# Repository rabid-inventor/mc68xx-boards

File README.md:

# mc68xx-boards
collection of PCB's based around the Motorola MC6800 series processor

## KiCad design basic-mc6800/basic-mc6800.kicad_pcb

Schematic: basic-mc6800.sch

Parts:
C1, C2, C3, C5, C6, C7, C8, C9: C_Small; C_0603
J1: Conn_01x39_Male; PinHeader_1x39_P2.54mm_Vertical
J2: Conn_01x04_Male; PinSocket_1x04_P2.54mm_Vertical
JP1, JP2, JP3: Jumper_2_Open; SolderJumper-2_P1.3mm_Bridged_RoundedPad1.0x1.5mm
MH1, MH2, MH3, MH4: MountingHole; MountingHole_3.2mm_M3_DIN965
R1, R2, R3, R4, R5, R6, R7, R8: R_Small; R_0603_1608Metric
U1: 74LV32; SOIC-14_3.9x8.7mm_Pitch1.27mm
U2: MC6809; DIP-40_W15.24mm
U3: IS61C256AL; DIP-28_W7.62mm
U4: 28C256; DIP-28_W15.24mm
U5: 74LV14; SOIC-14_3.9x8.7mm_Pitch1.27mm
Y1: ABLS-4.000MHZ-20-B-3-H-T; Crystal_SMD_HC49-SD

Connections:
+5V: C1.1, C5.1, C6.1, C7.1, C8.1, C9.1, J1.18, R1.1, R2.1, R3.1, R4.1, R5.1, R6.1, R7.1, R8.1, U1.14, U2.7, U3.28, U4.28, U5.14 (VCC)
/A0: J1.1, U2.8, U3.10, U4.10
/A1: J1.2, U2.9, U3.9, U4.9
/A2: J1.3, U2.10, U3.8, U4.8
/A3: J1.4, U2.11, U3.7, U4.7
/A4: J1.5, U2.12, U3.6, U4.6
/A5: J1.6, U2.13, U3.5, U4.5
/A6: J1.7, U2.14, U3.4, U4.4
/A7: J1.8, U2.15, U3.3, U4.3
/A8: J1.9, U2.16, U3.25, U4.25
/A9: J1.10, U2.17, U3.24, U4.24
/A10: J1.11, U2.18, U3.21, U4.21
/A11: J1.12, U2.19, U3.23, U4.23
/A12: J1.13, U1.1, U2.20, U3.2, U4.2
/A13: J1.14, U1.2, U2.21, U3.26, U4.26
/A14: J1.15, U1.9, U2.22, U3.1, U4.1
/A15: J1.16, U2.23, U3.20, U5.5
/BA: U2.6
/BS: U2.5
/D0: J1.27, U2.31, U3.11, U4.11
/D1: J1.28, U2.30, U3.12, U4.12
/D2: J1.29, U2.29, U3.13, U4.13
/D3: J1.30, U2.28, U3.15, U4.15
/D4: J1.31, U2.27, U3.16, U4.16
/D5: J1.32, U2.26, U3.17, U4.17
/D6: J1.33, U2.25, U3.18, U4.18
/D7: J1.34, U2.24, U3.19, U4.19
/E: J1.21, U2.34
/INT1: J1.22, R2.2, U2.2
/INT2: JP2.1, R3.2, U2.3
/INT3: JP3.1, R4.2, U2.4
/M1: J1.19
/MEM_REQ: J1.23
/MRDY: R7.2, U2.36
/PER_CS: J1.26, U1.6, U5.9
/QLATCH: U2.35, U5.3
/READ_OUT: J1.25, U5.2
/RESET: C1.2, J1.20, R1.2, U2.37
/ROM_CS: U1.11, U4.22
/RX: J1.35
/R_W: J1.24, U2.32, U3.27, U5.1
/TX: J1.36
/USR1: J1.37
/_A15: U1.10, U1.13, U5.6
/_DMA: R5.2, U2.33
/_HALT: R6.2, U2.40
/_QLATCH: U3.22, U4.20, U5.4
GND: C2.2, C3.2, C5.2, C6.2, C7.2, C8.2, C9.2, J1.17, U1.7, U2.1, U3.14, U4.14, U5.7 (GND)
unnamed: C2.1, U2.39, Y1.1
unnamed: C3.1, U2.38, Y1.2
unnamed: J1.38, JP2.2
unnamed: J1.39, JP3.2
unnamed: J2.1, U5.10
unnamed: J2.2, U5.11
unnamed: J2.3, U5.12
unnamed: J2.4, U5.13
unnamed: JP1.1, R8.2
unnamed: JP1.2, U4.27
unnamed: U1.3, U1.4
unnamed: U1.5, U1.8
unnamed: U1.12, U5.8

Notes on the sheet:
when q rises adress on bus iis valid
mrdy is used for streaching q and e high if not needed
BA= bus available
if 15 high = not available
use for data latch
when A15 high eeprom when low eeprom is active
chips used: MC6809 28C256 IS61C256AL 74LS137
https://www.sbprojects.net/projects/nano6802/index.php
Memory Map 0x9000 - 0xFFFF ROM 0x8000 - 0x8FFF PERF 0x0000 - 0x7FFF RAM
if dma is pulled low mpu will let go of busses and acknowledge by pullin gboth BA and BS high
DMA system Can be used for a DRAM refresh
b1000
b1001 - b1111
spare inverter

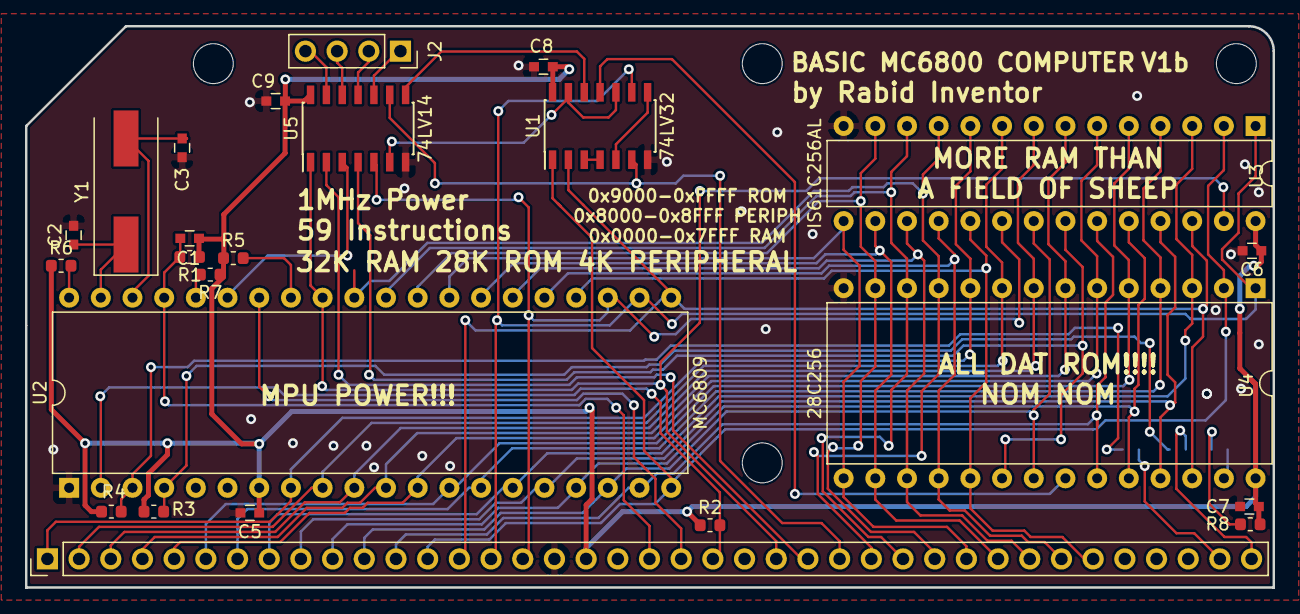
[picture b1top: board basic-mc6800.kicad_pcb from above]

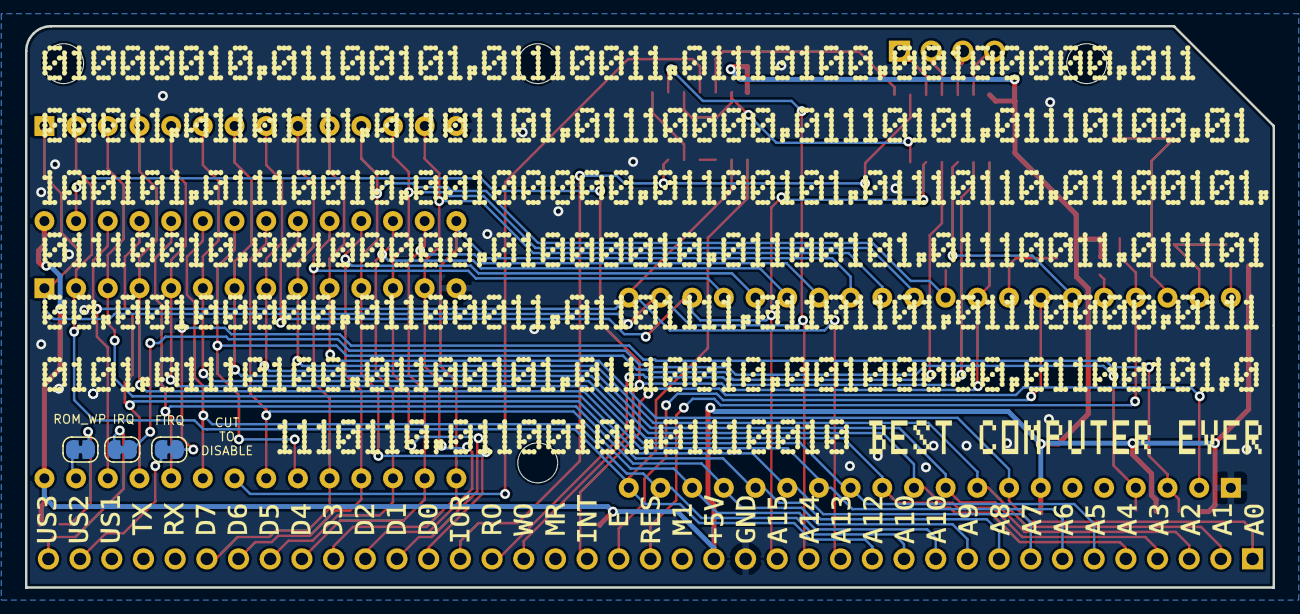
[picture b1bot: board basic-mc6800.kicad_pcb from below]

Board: 2 copper layers, 100.0 x 45.0 mm, 31 parts (3 on the bottom side), 54 nets.

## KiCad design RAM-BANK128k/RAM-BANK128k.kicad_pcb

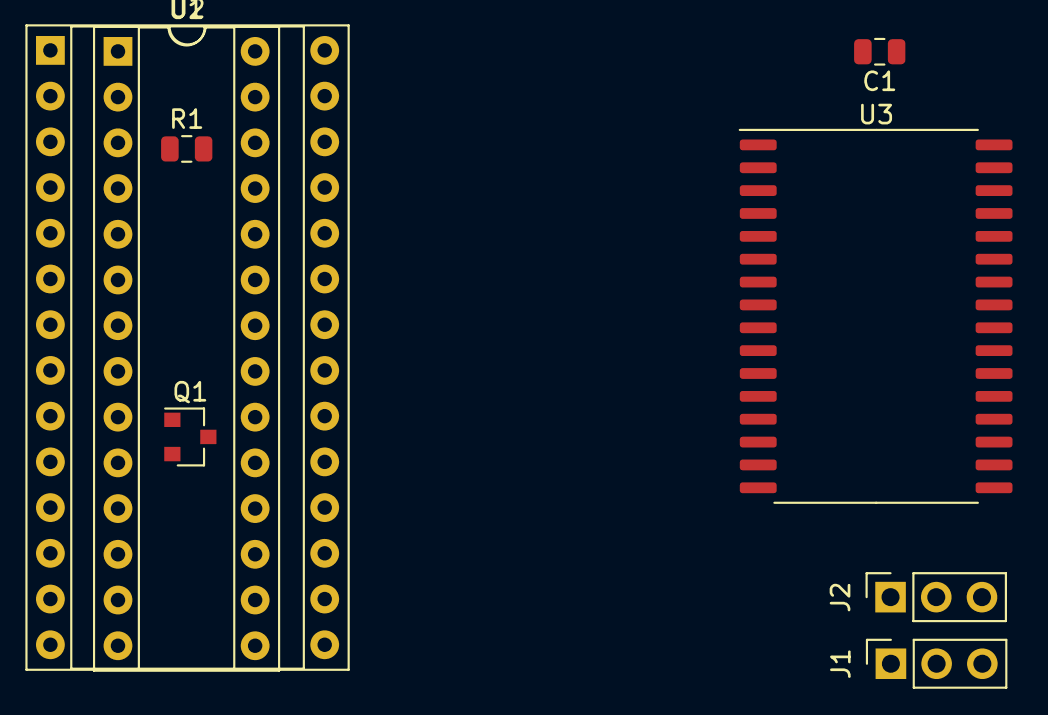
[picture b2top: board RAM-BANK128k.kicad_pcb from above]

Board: 2 copper layers, 8 parts (0 on the bottom side), 31 nets, no tracks yet.

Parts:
C1: C_Small; C_0805_2012Metric
J1, J2: Conn_01x03_Male; PinSocket_1x03_P2.54mm_Vertical
Q1: BSS138; SOT-23
R1: R_Small; R_0805_2012Metric
U1: IS61C256AL; DIP-28_W7.62mm_Socket
U2: 6C62256; DIP-28_W15.24mm_Socket
U3: HY628100B12; SSOP-32_11.305x20.495mm_P1.27mm

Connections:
+5V: C1.1, J1.1, J2.1, R1.1, U1.28, U2.28, U3.32
/A0: U1.10, U2.10, U3.12
/A1: U1.9, U2.9, U3.11
/A2: U1.8, U2.8, U3.10
/A3: U1.7, U2.7, U3.9
/A4: U1.6, U2.6, U3.8
/A5: U1.5, U2.5, U3.7
/A6: U1.4, U2.4, U3.6
/A7: U1.3, U2.3, U3.5
/A8: U1.25, U2.25, U3.27
/A9: U1.24, U2.24, U3.26
/A10: U1.21, U2.21, U3.23
/A11: U1.23, U2.23, U3.25
/A12: U1.2, U2.2, U3.4
/A13: U1.26, U2.26, U3.28
/A14: U1.1, U2.1, U3.3
/A15: J1.2, U3.31
/A16: J2.2, U3.2
/CS: Q1.3, R1.2, U3.30
/D1: U1.12, U2.12, U3.14
/D2: U1.13, U2.13, U3.15
/D3: U1.15, U2.15, U3.17
/D4: U1.16, U2.16, U3.18
/D5: U1.17, U2.17, U3.19
/D6: U1.18, U2.18, U3.20
/D7: U1.19, U2.19, U3.21
/DO: U1.11, U2.11, U3.13
/_CS: Q1.1, U1.20, U2.20, U3.22
/_OE: U1.22, U2.22, U3.24
/_WE: U1.27, U2.27, U3.29
GND: C1.2, J1.3, J2.3, Q1.2, U1.14, U2.14, U3.16

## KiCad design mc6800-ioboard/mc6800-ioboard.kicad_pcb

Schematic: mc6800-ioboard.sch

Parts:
C1, C2, C3, C4: C_Small; C_0603_1608Metric
D1, D2, D3: LED_ALT; LED_D5.0mm
DS1: WC1602A
J1: Conn_01x02_Female; PinHeader_1x02_P2.54mm_Vertical
J2: Conn_01x39_Male; PinHeader_1x39_P2.54mm_Vertical
J3: 10118193-0001LF; USB_Micro_B_Female_10118193-0001LF; MPN 10118193-0001LF; Digi-Key_PN 609-4616-1-ND
JP1: Jumper_NC_Small; SolderJumper-2_P1.3mm_Bridged_RoundedPad1.0x1.5mm
Q1: Q_NMOS_GSD; SOT-23
R1, R2, R3, R4: R_Small; R_0603_1608Metric
RV1: R_POT; Potentiometer_Vishay_T73YP_Vertical
SW1, SW2, SW3, SW4, SW5, SW6: SW_Push; SW_SPST_EVQPE1
U1, U2: 74LS32; DIP-14_W7.62mm
U3: 6822; DIP-40_W15.24mm

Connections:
+5V: C1.1, C2.1, C3.1, C4.1, DS1.2, DS1.15, J1.1, J2.18, J3.1, RV1.3, U1.14, U2.14, U3.20 (VCC), U3.22 (CS0)
/A0: J2.1, U3.36 (RS0)
/A1: J2.2, U3.35 (RS1)
/A2: J2.3, U3.39 (CA2)
/A3: J2.4, U3.19 (CB2)
/A4: J2.5, U3.24 (CS1)
/A5: J2.6, U1.12
/A6: J2.7, U1.10
/A7: J2.8, U1.9
/A8: J2.9, U1.5
/A9: J2.10, U1.4
/A10: J2.11, U1.2
/A11: J2.12, U1.1
/A12: J2.13
/A13: J2.14
/A14: J2.15
/A15: J2.16
/ADD_SEL: U2.8, U3.23 (~CS2)
/D0: J2.27, U3.33 (D0)
/D1: J2.28, U3.32 (D1)
/D2: J2.29, U3.31 (D2)
/D3: J2.30, U3.30 (D3)
/D4: J2.31, U3.29 (D4)
/D5: J2.32, U3.28 (D5)
/D6: J2.33, U3.27 (D6)
/D7: J2.34, U3.26 (D7)
/E: J2.21, U3.25 (ENABLE)
/INT1: J2.22
/INTA: U3.40 (CA1)
/INTB: JP1.1, U3.18 (CB1)
/IOINT_REQ: J2.38, U3.37 (~IRQB), U3.38 (~IRQA)
/IOREQ: J2.26, U1.13
/M1: J2.19
/MEM_RQ: J2.23
/PA.0: DS1.7, U3.2 (PA0)
/PA.1: DS1.8, U3.3 (PA1)
/PA.2: DS1.9, U3.4 (PA2)
/PA.3: DS1.10, U3.5 (PA3)
/PA.4: DS1.6, U3.6 (PA4)
/PA.5: DS1.5, U3.7 (PA5)
/PA.6: DS1.4, U3.8 (PA6)
/PA.7: Q1.1, R2.1, U3.9 (PA7)
/PB.0: R3.1, U3.10 (PB0)
/PB.1: R4.1, U3.11 (PB1)
/PB.2: R1.1, U3.12 (PB2)
/PB.3: SW1.1, SW2.1, U3.13 (PB3)
/PB.4: SW3.1, SW4.1, U3.14 (PB4)
/PB.5: SW5.1, SW6.1, U3.15 (PB5)
/PB.6: SW1.2, SW3.2, SW5.2, U2.12, U3.16 (PB6)
/PB.7: SW2.2, SW4.2, SW6.2, U2.13, U3.17 (PB7)
/RESET: J2.20, U3.34 (~RESET)
/RO: J2.25
/RX: J2.35
/R_W: J2.24, U3.21 (R/~W)
/TX: J2.36
/USR1: J2.37
/USR3: J2.39
GND: C1.2, C2.2, C3.2, C4.2, D1.1, D2.1, D3.1, DS1.1, DS1.16, J2.17, J3.5, J3.SH, Q1.2, R2.2, RV1.1, U1.7, U2.7, U3.1 (VSS)
unnamed: D1.2, R3.2
unnamed: D2.2, R4.2
unnamed: D3.2, R1.2
unnamed: DS1.3, RV1.2
unnamed: J1.2, Q1.3
unnamed: JP1.2, U2.11
unnamed: U1.3, U2.1
unnamed: U1.6, U2.2
unnamed: U1.8, U2.4
unnamed: U1.11, U2.5
unnamed: U2.3, U2.9
unnamed: U2.6, U2.10

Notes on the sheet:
0X8010 - 0X801F
sounder connection
Address Space

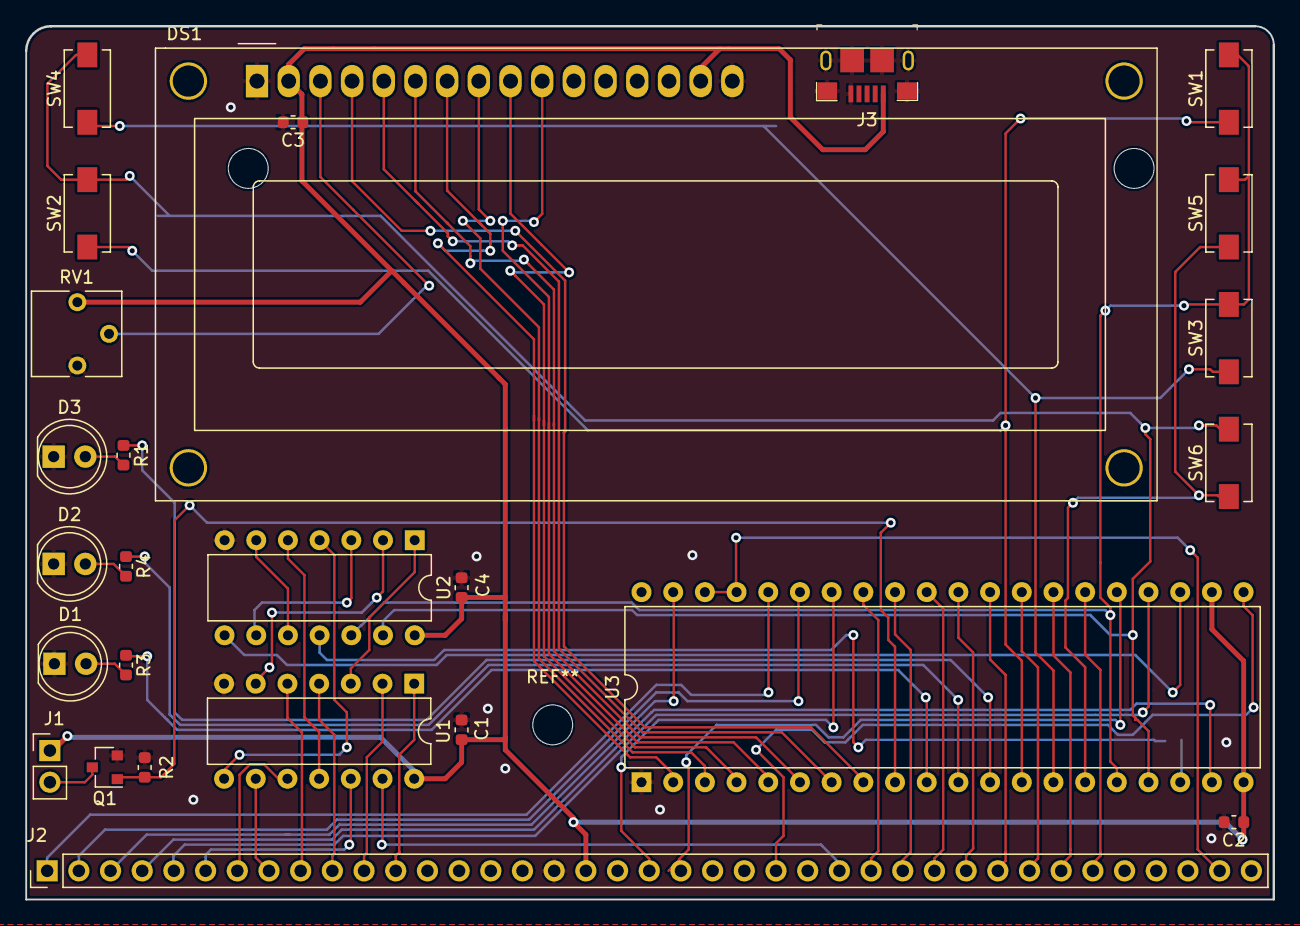
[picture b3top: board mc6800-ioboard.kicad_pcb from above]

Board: 2 copper layers, 100.0 x 70.0 mm, 27 parts (1 on the bottom side), 57 nets.

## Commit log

2020-02-27 first commit and notes
2020-02-29 Finished schmatic
2020-02-29 mover Per_cs to pinheader
2020-03-02 Finished routing and DRC check
2020-03-04 swapped rom to top of memory and some fixes DRC done
2020-03-04 added bottom silk
2020-03-05 silks done tied mrdy high gerder gened
2020-03-05 tidied some traces and started io board v1 gerber here
2020-03-05 added mc6822 datasheet
2020-03-09 schematic complete and started to route
2020-03-09 more routing
2020-03-10 routing mostly dome some tidying needeed
2020-03-10 started work on some example assembly
2020-03-11 sync checkpoint
2020-03-12 checkpoint sync
2020-03-12 reducing board size
2020-03-13 drc complete on io board and started logic for device select
2020-03-13 started on version 1.1
2020-03-26 changed part vaules to match what is available
2020-04-01 added pull ups for DMA and HALT
2020-04-03 backup checkin
2020-04-03 COMPLETE V1B BASICMC6900 started battery backed 128K banked ram
2020-04-08 added idea for bank switchble 128k ram
2020-04-22 moved clock output to clk pin
2020-08-03 final tweaks and created gerber
